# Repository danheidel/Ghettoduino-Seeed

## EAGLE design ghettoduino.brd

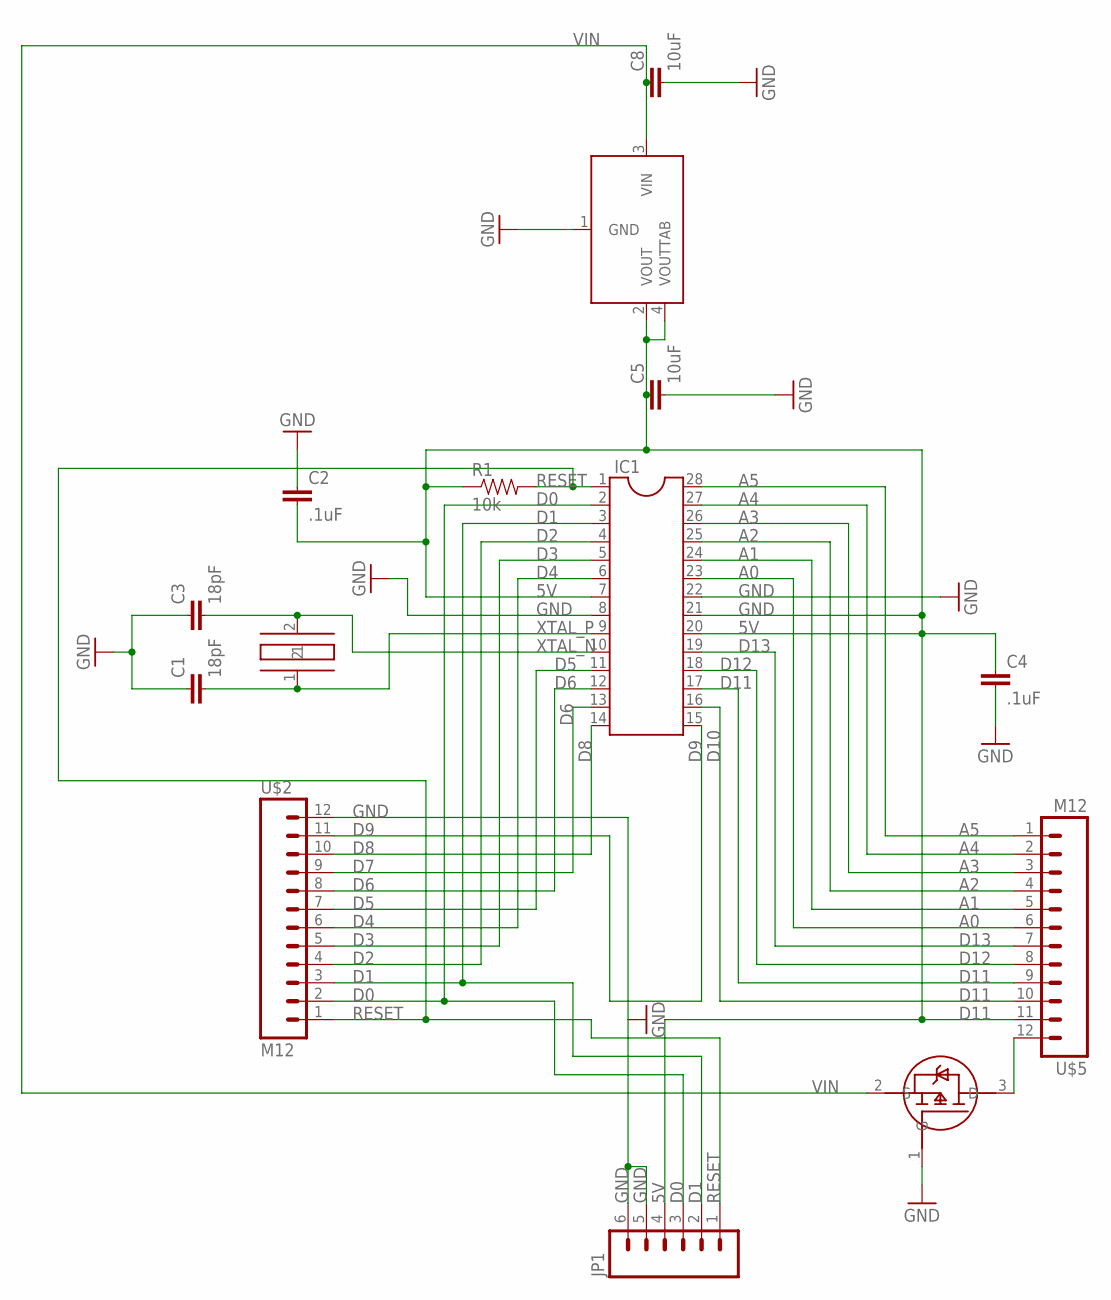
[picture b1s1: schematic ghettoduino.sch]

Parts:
5V: 5V-LDO-ZLDO1117; ZLDO1117
C1, C3: 18pF; 0603-CAP
C2, C4: .1uF; 0805
C5, C8: 10uF; 1206
IC1: DIL28-3
JP1: M06LOCK; 1X06_LOCK
R1: 10k; 0805
U$1: HC49US
U$2, U$5: M12; 1X12_LOCK
U$3: P-MOSFET-PMV48XP; SOT23-3LEAD

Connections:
5V: 5V.2 (VOUT), 5V.4 (VOUTTAB), C2.2, C4.1, C5.1, IC1.7, IC1.20, IC1.21, JP1.4, R1.1, U$5.11
A0: IC1.23, U$5.6
A1: IC1.24, U$5.5
A2: IC1.25, U$5.4
A3: IC1.26, U$5.3
A4: IC1.27, U$5.2
A5: IC1.28, U$5.1
D0: IC1.2, JP1.3, U$2.2
D1: IC1.3, JP1.2, U$2.3
D2: IC1.4, U$2.4
D3: IC1.5, U$2.5
D4: IC1.6, U$2.6
D5: IC1.11, U$2.7
D6: IC1.12, U$2.8
D7: IC1.13, U$2.9
D8: IC1.14, U$2.10
D9: IC1.15, U$2.11
D10: IC1.16, U$5.10
D11: IC1.17, U$5.9
D12: IC1.18, U$5.8
D13: IC1.19, U$5.7
GND: 5V.1 (GND), C1.1, C2.1, C3.1, C4.2, C5.2, C8.2, IC1.8, IC1.22, JP1.5, JP1.6, U$2.12, U$2.13, U$3.1 (G)
unnamed: U$3.3 (D), U$5.12
RESET: IC1.1, JP1.1, R1.2, U$2.1
VIN: 5V.3 (VIN), C8.1, U$3.2 (S)
XTAL_N: C3.2, IC1.10, U$1.2
XTAL_P: C1.2, IC1.9, U$1.1

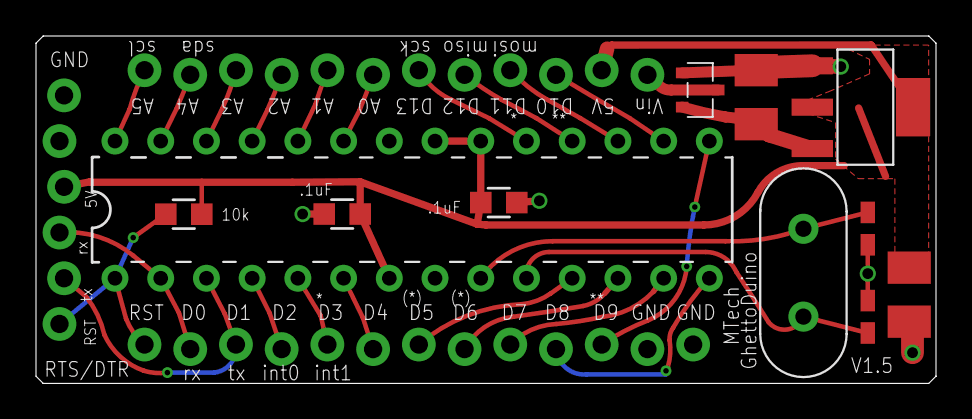
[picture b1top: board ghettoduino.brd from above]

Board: 2 copper layers, 50.0 x 19.3 mm, 14 parts (0 on the bottom side), 27 nets.

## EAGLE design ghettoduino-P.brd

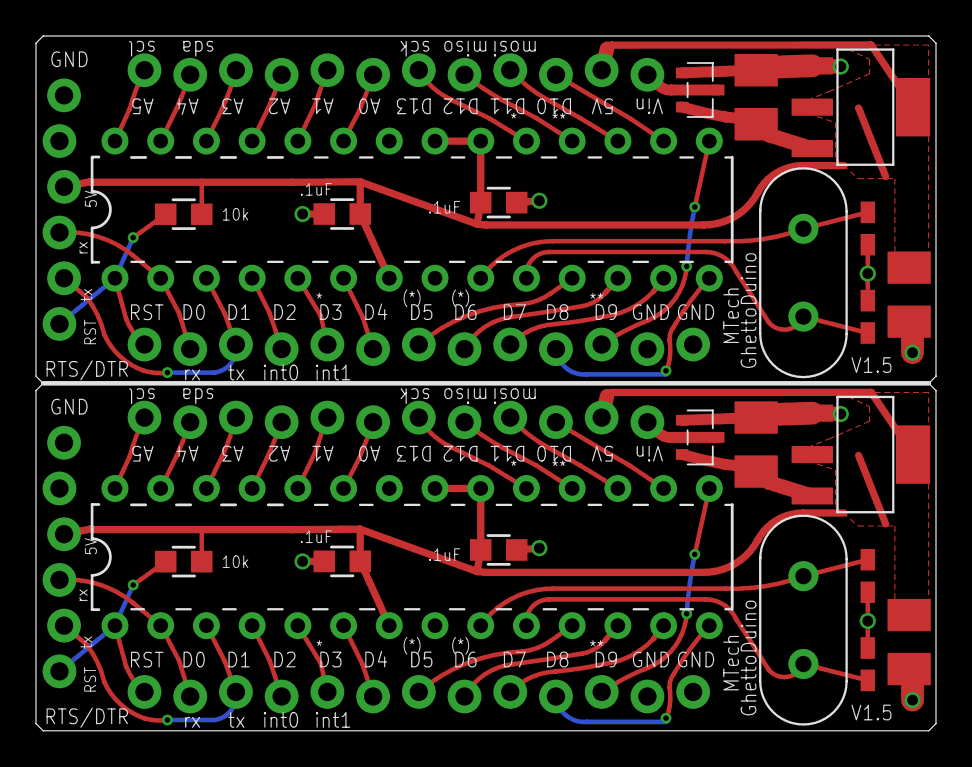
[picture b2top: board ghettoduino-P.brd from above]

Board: 2 copper layers, 50.0 x 38.6 mm, 28 parts (0 on the bottom side), 54 nets.

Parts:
5V, 5V1: 5V-LDO-ZLDO1117; ZLDO1117
C1, C3, C6, C7: 18pF; 0603-CAP
C2, C4, C9, C10: .1uF; 0805
C5, C8, C11, C12: 10uF; 1206
IC1, IC2: DIL28-3
JP1, JP2: 1X06_LOCK
R1, R2: 10k; 0805
U$1, U$4: HC49US
U$2, U$6: M12; 1X13_LOCK
U$3, U$8: P-MOSFET-PMV48XP; SOT23-3LEAD
U$5, U$7: M12; 1X12_LOCK

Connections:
5V: 5V.2, 5V.4, C2.2, C4.1, C5.1, IC1.7, IC1.20, IC1.21, JP1.4, R1.1, U$5.11
5V1: 5V1.2, 5V1.4, C9.2, C10.1, C11.1, IC2.7, IC2.20, IC2.21, JP2.4, R2.1, U$7.11
A0: IC1.23, U$5.6
A1: IC1.24, U$5.5
A2: IC1.25, U$5.4
A3: IC1.26, U$5.3
A4: IC1.27, U$5.2
A5: IC1.28, U$5.1
A6: IC2.28, U$7.1
A7: IC2.27, U$7.2
A8: IC2.26, U$7.3
A9: IC2.25, U$7.4
A10: IC2.24, U$7.5
A11: IC2.23, U$7.6
D0: IC1.2, JP1.3, U$2.2
D1: IC1.3, JP1.2, U$2.3
D2: IC1.4, U$2.4
D3: IC1.5, U$2.5
D4: IC1.6, U$2.6
D5: IC1.11, U$2.7
D6: IC1.12, U$2.8
D7: IC1.13, U$2.9
D8: IC1.14, U$2.10
D9: IC1.15, U$2.11
D10: IC1.16, U$5.10
D11: IC1.17, U$5.9
D12: IC1.18, U$5.8
D13: IC1.19, U$5.7
D14: IC2.4, U$6.4
D15: IC2.5, U$6.5
D16: IC2.6, U$6.6
D17: IC2.11, U$6.7
D18: IC2.12, U$6.8
D19: IC2.13, U$6.9
D20: IC2.14, U$6.10
D21: IC2.15, U$6.11
D22: IC2.16, U$7.10
D23: IC2.17, U$7.9
D24: IC2.18, U$7.8
D25: IC2.19, U$7.7
D26: IC2.2, JP2.3, U$6.2
D27: IC2.3, JP2.2, U$6.3
GND: 5V.1, C1.1, C2.1, C3.1, C4.2, C5.2, C8.2, IC1.8, IC1.22, JP1.5, JP1.6, U$2.12, U$2.13, U$3.1
GND1: 5V1.1, C6.1, C7.1, C9.1, C10.2, C11.2, C12.2, IC2.8, IC2.22, JP2.5, JP2.6, U$6.12, U$6.13, U$8.1
unnamed: U$3.3, U$5.12
unnamed: U$7.12, U$8.3
RESET: IC1.1, JP1.1, R1.2, U$2.1
RESET1: IC2.1, JP2.1, R2.2, U$6.1
VIN: 5V.3, C8.1, U$3.2
VIN1: 5V1.3, C12.1, U$8.2
XTAL_N: C3.2, IC1.10, U$1.2
XTAL_N1: C6.2, IC2.10, U$4.2
XTAL_P: C1.2, IC1.9, U$1.1
XTAL_P1: C7.2, IC2.9, U$4.1

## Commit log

2011-11-03 Doubled ghettoduino for production through Seeedstudios.
2011-11-11 De-fake panelized, actually panelized the boards.
2011-11-22 Tweaked the PS bypass caps, also got rid of the low clearance between Vin and 5V on the heatsink poly under the PS. Also eps cream files.
2011-12-08 Panelization redone the proper way. Single copy in ghettoduino.brd/sch files. ghettoduino-P.brd has the panelized version for making Gerbers.
2011-12-08 Remade outline and paste files, new gerber files and zip.
2011-12-08 Cleaned up the .sch. Added labels and renamed some wires.
2011-12-24 Rev to 1.5 Deleted Eagle internal backup files, Git makes them redundant and they clutter the file listings. Added lots of helpful labels to the board. Shrank the board Y dimension a bit. Flipped som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
2011-12-24 More file cleanup -updated outline and creme files -added creme suffix to creme filenames
2012-01-10 Added p-channel MOSFET for reverse power protection.
    Gerber, eps files still need update.
2012-03-06 Added p-FET reverse bias protection, more markings, extra ground pin, general re-arranging and cleanup.
2012-03-06 Panelized with new design.
2012-03-08 Deleted unused .zip files, redid panelization, panelized Gerber files, new .eps files.
2012-03-16 New .eps export, tweaked in Inkscape.
2012-03-16 fixed .eps line widths
2012-03-17 Fixed errors in .eps files.
2012-04-26 minor edits, tweaks to .eps files
